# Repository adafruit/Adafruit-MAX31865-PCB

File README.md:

## Adafruit MAX31865 PCB

<a href="http://www.adafruit.com/products/3328"><br/>
Click here to purchase one from the Adafruit shop</a>

PCB files for the Adafruit MAX31865 RTD Sensor Breakout. Format is EagleCAD schematic and board layout
* https://www.adafruit.com/product/3328

### Description

For precision temperature sensing, nothing beats a Platinum RTD. Resistance temperature detectors (RTDs) are temperature sensors that contain a resistor that changes resistance value as its temperature changes, basically a kind of thermistor. In this sensor, the resistor is actually a small strip of Platinum with a resistance of 100 ohms at 0°C, thus the name PT100. Compared to most NTC/PTC thermistors, the PT type of RTD is much most stable and precise (but also more expensive) PT100's have been used for many years to measure temperature in laboratory and industrial processes, and have developed a reputation for accuracy (better than thermocouples), repeatability, and stability. 

However, to get that precision and accuracy out of your PT100 RTD you must use an amplifier that is designed to read the low resistance. Better yet, have an amplifier that can automatically adjust and compensate for the resistance of the connecting wires. If you're looking for a great RTD sensor, today is your lucky day because we have a lovely Adafruit RTD Sensor Amplifier with the MAX31865 breakout for use with any 2, 3 or 4 wire PT100 RTD!

### License

Adafruit invests time and resources providing this open source design, please support Adafruit and open-source hardware by purchasing products from [Adafruit](https://www.adafruit.com)!

Designed by Limor Fried/Ladyada for Adafruit Industries.

Creative Commons Attribution/Share-Alike, all text above must be included in any redistribution. See license.txt for additional details.

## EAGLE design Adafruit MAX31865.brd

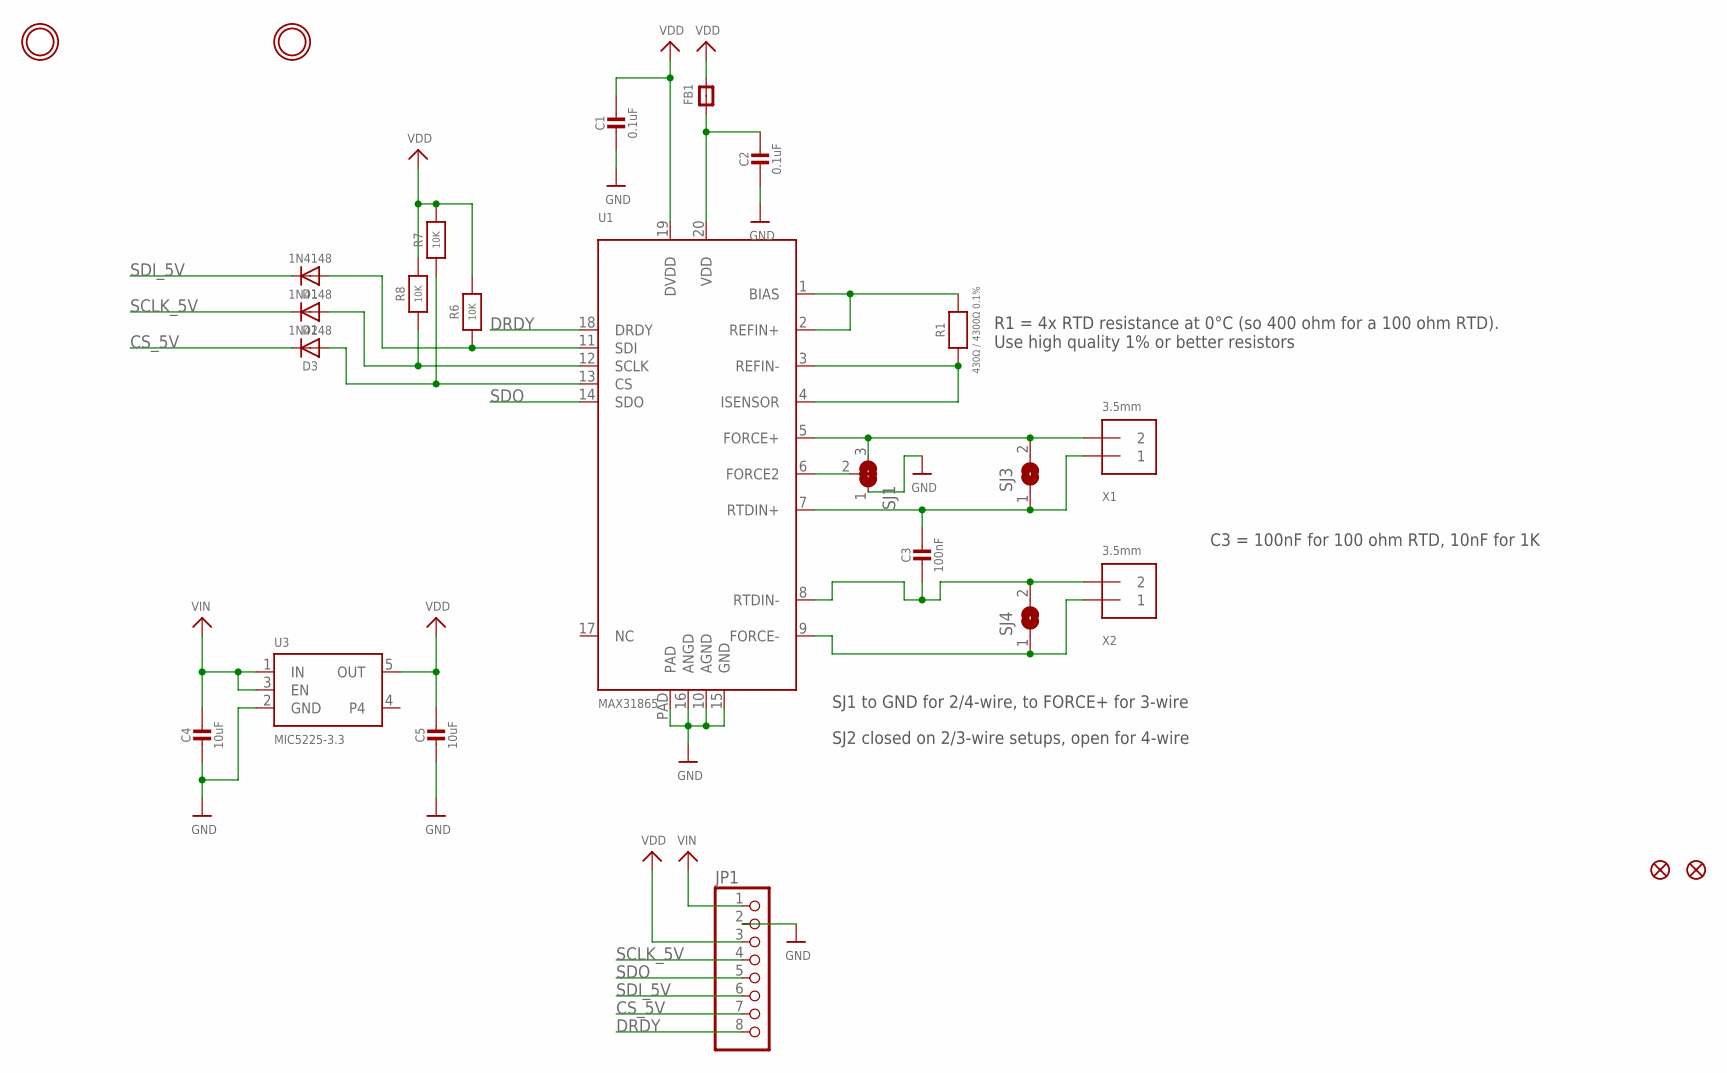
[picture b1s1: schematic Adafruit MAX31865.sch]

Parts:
C1, C2: 0.1uF; 0805-NO
C3: 100nF; 0805-NO
C4, C5: 10uF; 0805-NO
D1, D2, D3: 1N4148; SOD-323
FB1: FERRITE-0805NO; 0805-NO
FID1, FID2: FIDUCIAL""; FIDUCIAL_1MM
JP1: HEADER-1X870MIL; 1X08_ROUND_70
R1: 430Ω / 4300Ω 0.1%; 0805-NO
R6, R7, R8: 10K; 0805-NO
SJ1: SOLDERJUMPER_2WAY; SOLDERJUMPER_2WAY_OPEN_NOPASTE
SJ3, SJ4: SOLDERJUMPER; SOLDERJUMPER_ARROW_NOPASTE
U1: MAX31865; QFN20_4MM_0.65MM
U3: MIC5225-3.3; SOT23-5
U$18, U$19: MOUNTINGHOLE2.5; MOUNTINGHOLE_2.5_PLATED
X1, X2: 3.5mm; TERMBLOCK_1X2-3.5MM

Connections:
CS_5V: D3.C, JP1.7
DRDY: JP1.8, U1.18 (DRDY)
FORCE+: SJ1.3, SJ3.2, U1.5 (FORCE+), X1.2
FORCE-: SJ4.1, U1.9 (FORCE-), X2.1
GND: C1.2, C2.2, C4.2, C5.2, JP1.2, SJ1.1, U1.10 (AGND), U1.15 (GND), U1.16 (ANGD), U1.PAD, U3.2 (GND)
unnamed: R1.1, U1.3 (REFIN-), U1.4 (ISENSOR)
unnamed: R1.2, U1.1 (BIAS), U1.2 (REFIN+)
unnamed: C2.1, FB1.1, U1.20 (VDD)
unnamed: SJ1.2, U1.6 (FORCE2)
unnamed: D3.A, R7.1, U1.13 (CS)
unnamed: D2.A, R8.1, U1.12 (SCLK)
unnamed: D1.A, R6.1, U1.11 (SDI)
RTDIN+: C3.1, SJ3.1, U1.7 (RTDIN+), X1.1
RTDIN-: C3.2, SJ4.2, U1.8 (RTDIN-), X2.2
SCLK_5V: D2.C, JP1.4
SDI_5V: D1.C, JP1.6
SDO: JP1.5, U1.14 (SDO)
VDD: C1.1, C5.1, FB1.2, JP1.3, R6.2, R7.2, R8.2, U1.19 (DVDD), U3.5 (OUT)
VIN: C4.1, JP1.1, U3.1 (IN), U3.3 (EN)

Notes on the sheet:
C3 = 100nF for 100 ohm RTD, 10nF for 1K
R1 = 4x RTD resistance at 0°C (so 400 ohm for a 100 ohm RTD). Use high quality 1% or better resistors
SJ1 to GND for 2/4-wire, to FORCE+ for 3-wire
SJ2 closed on 2/3-wire setups, open for 4-wire

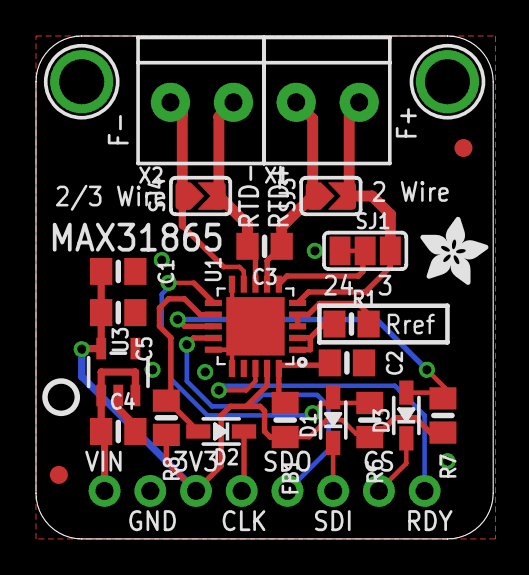
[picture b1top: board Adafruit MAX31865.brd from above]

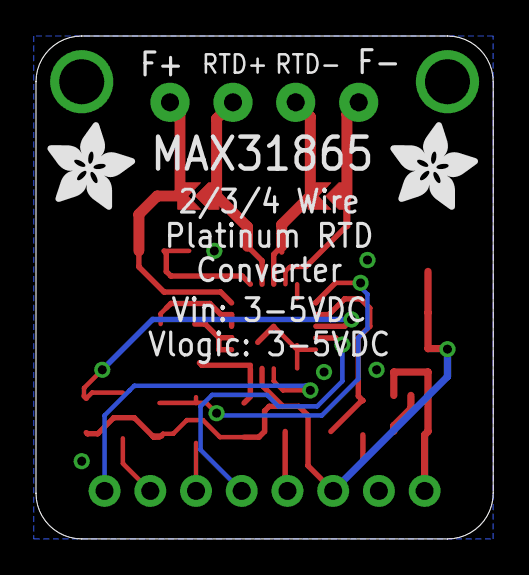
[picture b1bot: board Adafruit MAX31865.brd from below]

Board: 2 copper layers, 25.4 x 27.9 mm, 29 parts (2 on the bottom side), 19 nets.

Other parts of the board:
U$8: PCBFEAT-REV-040
U$16: ADAFRUIT_3.5MM
U$20, U$21: ADAFRUIT_5MM

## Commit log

2016-11-15 init

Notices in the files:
parts and their libraries:
microbuilder: This work is placed in the public domain, and may be freely used for commercial and non-commercial work with the following conditions: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
